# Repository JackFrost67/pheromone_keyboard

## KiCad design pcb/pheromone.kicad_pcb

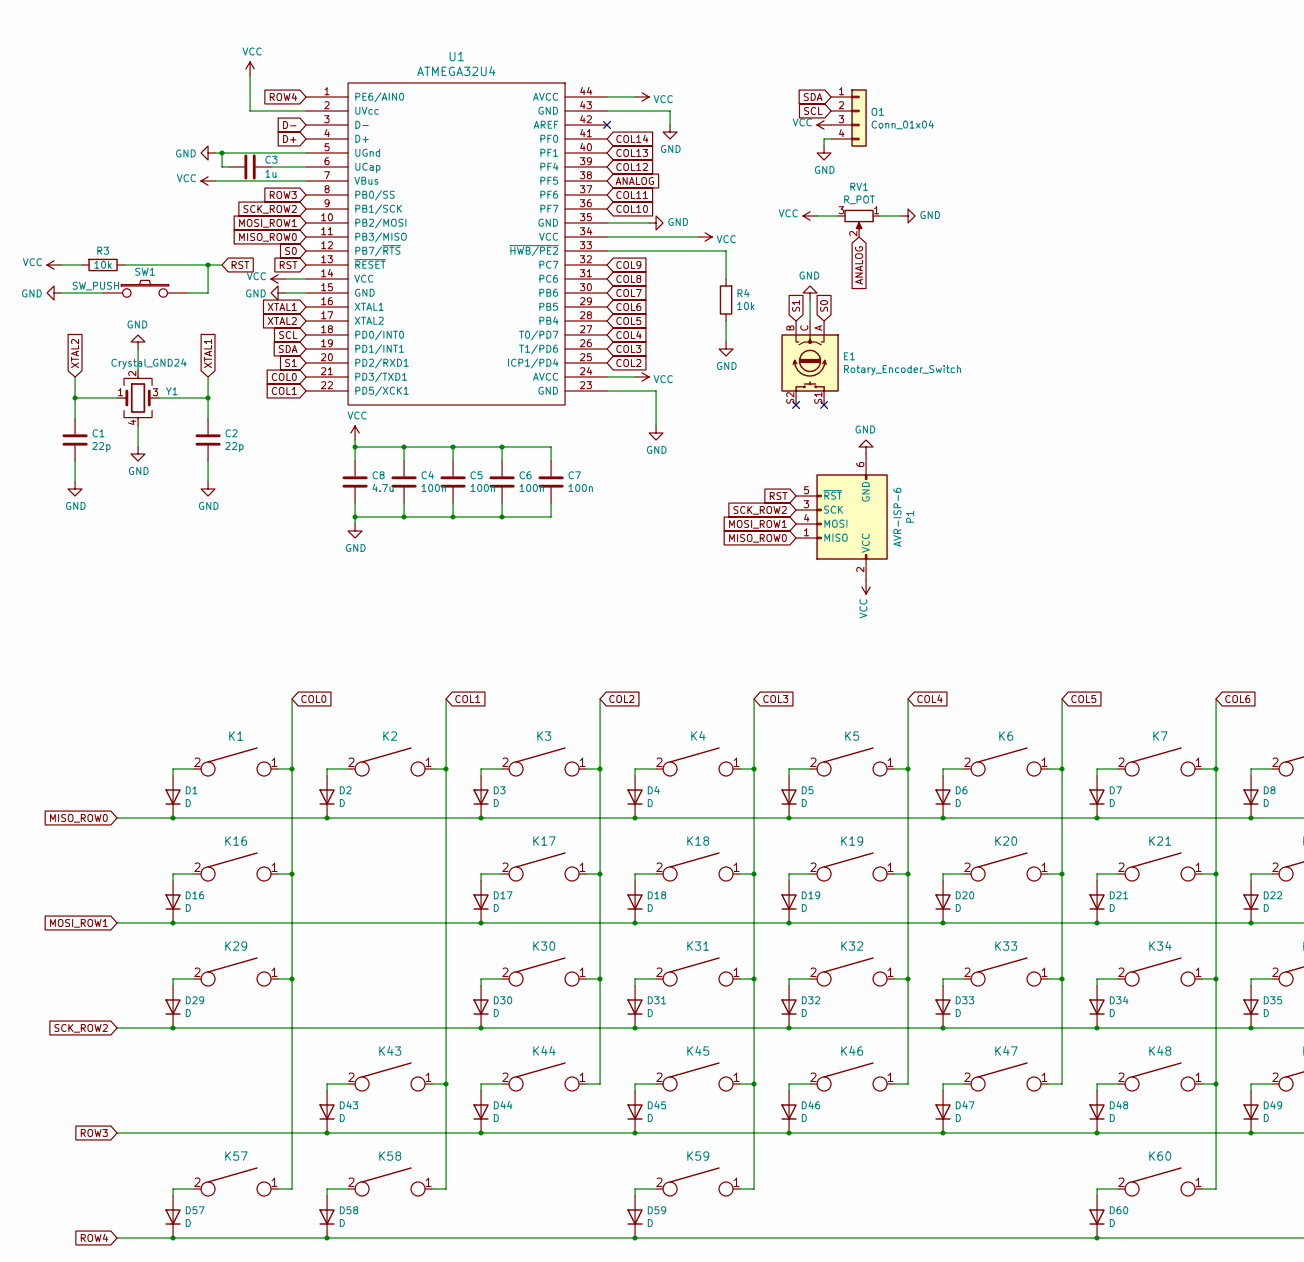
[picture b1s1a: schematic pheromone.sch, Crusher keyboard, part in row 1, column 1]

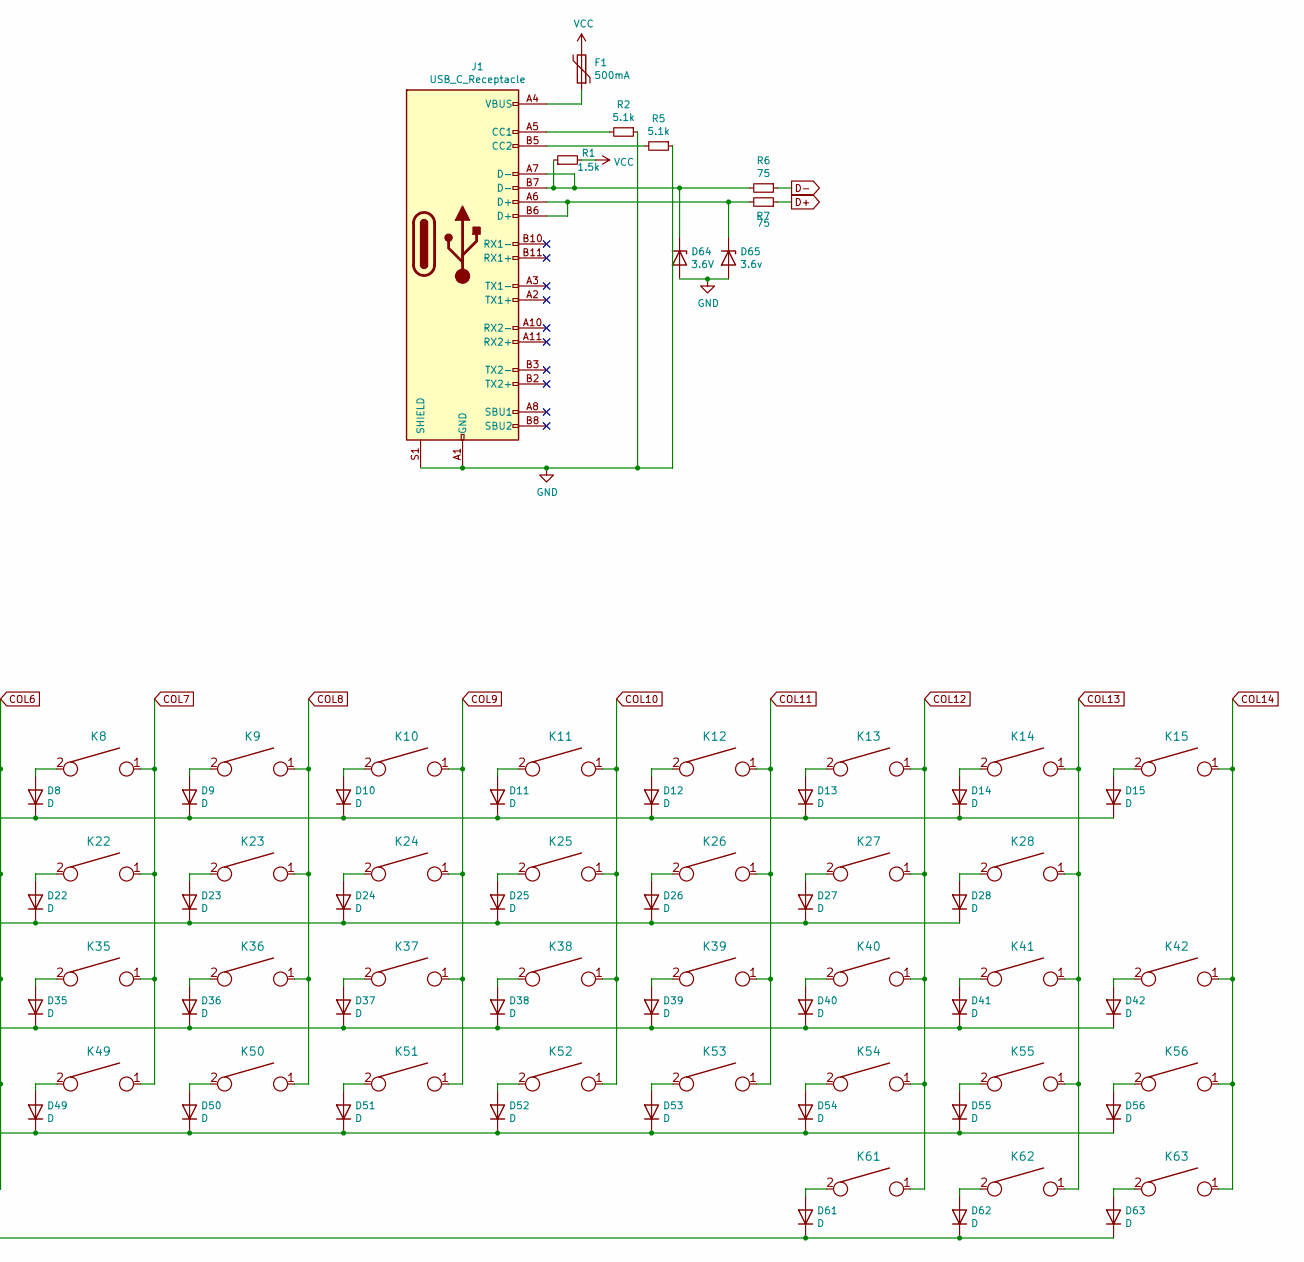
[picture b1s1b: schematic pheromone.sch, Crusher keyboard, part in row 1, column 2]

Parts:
C1, C2: 22p; C_0805_2012Metric
C3: 1u; C_0805_2012Metric
C4, C5, C6, C7: 100n; C_0805_2012Metric
C8: 4.7u; C_0805_2012Metric
D1, D2, D3, D4, D5, D6, D7, D8, D9, D10, D11, D12, D13, D14, D15, D16, D17, D18, D19, D20, D21, D22, D23, D24, D25, D26, D27, D28, D29, D30, D31, D32, D33, D34, D35, D36, D37, D38, D39, D40, D41, D42, D43, D44, D45, D46, D47, D48, D49, D50, D51, D52, D53, D54, D55, D56, D57, D58, D59, D60, D61, D62, D63: D; D_SOD-123
D64: 3.6V; D_SOD-123
D65: 3.6v; D_SOD-123
E1: Rotary_Encoder_Switch; RotaryEncoder_Alps_EC11E-Switch_Vertical_H20mm
F1: 500mA; Fuse_0805_2012Metric
J1: USB_C_Receptacle; USB_C_Receptacle_GCT_USB4085
K1, K2, K3, K4, K5, K6, K7, K8, K9, K10, K11, K12, K13, K14, K15, K17, K18, K19, K20, K21, K22, K23, K24, K25, K26, K27, K28, K30, K31, K32, K33, K34, K35, K36, K37, K38, K39, K40, K41, K44, K45, K46, K47, K48, K49, K50, K51, K52, K53, K54, K55, K56, K61, K62, K63: KEYSW; MXOnly-1U-Hotswap
K16: KEYSW; MXOnly-1.5U-Hotswap
K29: KEYSW; MXOnly-1.75U-Hotswap
K42: KEYSW; MXOnly-ISO-Hotswap
K43: KEYSW; MXOnly-2U-Hotswap-ReversedStabilizers
K57, K58, K59: KEYSW; MXOnly-1.25U-Hotswap
K60: KEYSW; MXOnly-6.25U-Hotswap-ReversedStabilizers
O1: Conn_01x04; 0.91_SSD1306_OLED
P1: AVR-ISP-6; PinHeader_2x03_P2.54mm_Vertical
R1: 1.5k; R_0805_2012Metric
R2, R5: 5.1k; R_0805_2012Metric
R3, R4: 10k; R_0805_2012Metric
R6, R7: 75; R_0805_2012Metric
RV1: R_POT; potentiometer_slider_45mm
SW1: SW_PUSH; SW_DIP_SPSTx01_Slide_6.7x4.1mm_W6.73mm_P2.54mm_LowProfile_J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
U1: ATMEGA32U4; TQFP-44_10x10mm_Pitch0.8mm
Y1: Crystal_GND24; Crystal_SMD_3225-4Pin_3.2x2.5mm

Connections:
ANALOG: RV1.2, U1.38 (PF5)
COL0: K1.1, K16.1, K29.1, K57.1, U1.21 (PD3/TXD1)
COL1: K2.1, K43.1, K58.1, U1.22 (PD5/XCK1)
COL2: K3.1, K17.1, K30.1, K44.1, U1.25 (ICP1/PD4)
COL3: K4.1, K18.1, K31.1, K45.1, K59.1, U1.26 (T1/PD6)
COL4: K5.1, K19.1, K32.1, K46.1, U1.27 (T0/PD7)
COL5: K6.1, K20.1, K33.1, K47.1, U1.28 (PB4)
COL6: K7.1, K21.1, K34.1, K48.1, K60.1, U1.29 (PB5)
COL7: K8.1, K22.1, K35.1, K49.1, U1.30 (PB6)
COL8: K9.1, K23.1, K36.1, K50.1, U1.31 (PC6)
COL9: K10.1, K24.1, K37.1, K51.1, U1.32 (PC7)
COL10: K11.1, K25.1, K38.1, K52.1, U1.36 (PF7)
COL11: K12.1, K26.1, K39.1, K53.1, U1.37 (PF6)
COL12: K13.1, K27.1, K40.1, K54.1, K61.1, U1.39 (PF4)
COL13: K14.1, K28.1, K41.1, K55.1, K62.1, U1.40 (PF1)
COL14: K15.1, K42.1, K56.1, K63.1, U1.41 (PF0)
D+: R7.1, U1.4 (D+)
D-: R6.1, U1.3 (D-)
GND: C1.1, C2.1, C3.1, C4.1, C5.1, C6.1, C7.1, C8.1, D64.2 (A), D65.2 (A), E1.C, J1.A1 (GND), J1.A12 (GND), J1.B1 (GND), J1.B12 (GND), J1.S1 (SHIELD), O1.4, P1.6 (GND), R2.1, R4.1, R5.1, RV1.1, SW1.1, U1.5 (UGnd), U1.15 (GND), U1.23 (GND), U1.35 (GND), U1.43 (GND), Y1.2, Y1.4
MISO_ROW0: D1.1 (K), D2.1 (K), D3.1 (K), D4.1 (K), D5.1 (K), D6.1 (K), D7.1 (K), D8.1 (K), D9.1 (K), D10.1 (K), D11.1 (K), D12.1 (K), D13.1 (K), D14.1 (K), D15.1 (K), P1.1 (MISO), U1.11 (PB3/MISO)
MOSI_ROW1: D16.1 (K), D17.1 (K), D18.1 (K), D19.1 (K), D20.1 (K), D21.1 (K), D22.1 (K), D23.1 (K), D24.1 (K), D25.1 (K), D26.1 (K), D27.1 (K), D28.1 (K), P1.4 (MOSI), U1.10 (PB2/MOSI)
unnamed: C3.2, U1.6 (UCap)
unnamed: D1.2 (A), K1.2
unnamed: D2.2 (A), K2.2
unnamed: D3.2 (A), K3.2
unnamed: D4.2 (A), K4.2
unnamed: D5.2 (A), K5.2
unnamed: D6.2 (A), K6.2
unnamed: D7.2 (A), K7.2
unnamed: D8.2 (A), K8.2
unnamed: D9.2 (A), K9.2
unnamed: D10.2 (A), K10.2
unnamed: D11.2 (A), K11.2
unnamed: D12.2 (A), K12.2
unnamed: D13.2 (A), K13.2
unnamed: D14.2 (A), K14.2
unnamed: D15.2 (A), K15.2
unnamed: D16.2 (A), K16.2
unnamed: D17.2 (A), K17.2
unnamed: D18.2 (A), K18.2
unnamed: D19.2 (A), K19.2
unnamed: D20.2 (A), K20.2
unnamed: D21.2 (A), K21.2
unnamed: D22.2 (A), K22.2
unnamed: D23.2 (A), K23.2
unnamed: D24.2 (A), K24.2
unnamed: D25.2 (A), K25.2
unnamed: D26.2 (A), K26.2
unnamed: D27.2 (A), K27.2
unnamed: D28.2 (A), K28.2
unnamed: D29.2 (A), K29.2
unnamed: D30.2 (A), K30.2
unnamed: D31.2 (A), K31.2
unnamed: D32.2 (A), K32.2
unnamed: D33.2 (A), K33.2
unnamed: D34.2 (A), K34.2
unnamed: D35.2 (A), K35.2
unnamed: D36.2 (A), K36.2
unnamed: D37.2 (A), K37.2
unnamed: D38.2 (A), K38.2
unnamed: D39.2 (A), K39.2
unnamed: D40.2 (A), K40.2
unnamed: D41.2 (A), K41.2
unnamed: D42.2 (A), K42.2
unnamed: D43.2 (A), K43.2
unnamed: D44.2 (A), K44.2
unnamed: D45.2 (A), K45.2
unnamed: D46.2 (A), K46.2
unnamed: D47.2 (A), K47.2
unnamed: D48.2 (A), K48.2
unnamed: D49.2 (A), K49.2
unnamed: D50.2 (A), K50.2
unnamed: D51.2 (A), K51.2
unnamed: D52.2 (A), K52.2
unnamed: D53.2 (A), K53.2
unnamed: D54.2 (A), K54.2
unnamed: D55.2 (A), K55.2
unnamed: D56.2 (A), K56.2
unnamed: D57.2 (A), K57.2
unnamed: D58.2 (A), K58.2
unnamed: D59.2 (A), K59.2
unnamed: D60.2 (A), K60.2
unnamed: D61.2 (A), K61.2
unnamed: D62.2 (A), K62.2
unnamed: D63.2 (A), K63.2
unnamed: D64.1 (K), J1.A7 (D-), J1.B7 (D-), R1.1, R6.2
unnamed: D65.1 (K), J1.A6 (D+), J1.B6 (D+), R7.2
unnamed: F1.1, J1.A4 (VBUS), J1.A9 (VBUS), J1.B4 (VBUS), J1.B9 (VBUS)
unnamed: J1.A5 (CC1), R2.2
unnamed: J1.B5 (CC2), R5.2
unnamed: R4.2, U1.33 (~HWB/PE2)
ROW3: D43.1 (K), D44.1 (K), D45.1 (K), D46.1 (K), D47.1 (K), D48.1 (K), D49.1 (K), D50.1 (K), D51.1 (K), D52.1 (K), D53.1 (K), D54.1 (K), D55.1 (K), D56.1 (K), U1.8 (PB0/SS)
ROW4: D57.1 (K), D58.1 (K), D59.1 (K), D60.1 (K), D61.1 (K), D62.1 (K), D63.1 (K), U1.1 (PE6/AIN0)
RST: P1.5 (~RST), R3.1, SW1.2, U1.13 (~RESET)
S0: E1.A, U1.12 (PB7/~RTS)
S1: E1.B, U1.20 (PD2/RXD1)
SCK_ROW2: D29.1 (K), D30.1 (K), D31.1 (K), D32.1 (K), D33.1 (K), D34.1 (K), D35.1 (K), D36.1 (K), D37.1 (K), D38.1 (K), D39.1 (K), D40.1 (K), D41.1 (K), D42.1 (K), P1.3 (SCK), U1.9 (PB1/SCK)
SCL: O1.2, U1.18 (PD0/INT0)
SDA: O1.1, U1.19 (PD1/INT1)
VCC: C4.2, C5.2, C6.2, C7.2, C8.2, F1.2, O1.3, P1.2 (VCC), R1.2, R3.2, RV1.3, U1.2 (UVcc), U1.7 (VBus), U1.14 (VCC), U1.24 (AVCC), U1.34 (VCC), U1.44 (AVCC)
XTAL1: C2.2, U1.16 (XTAL1), Y1.3
XTAL2: C1.2, U1.17 (XTAL2), Y1.1

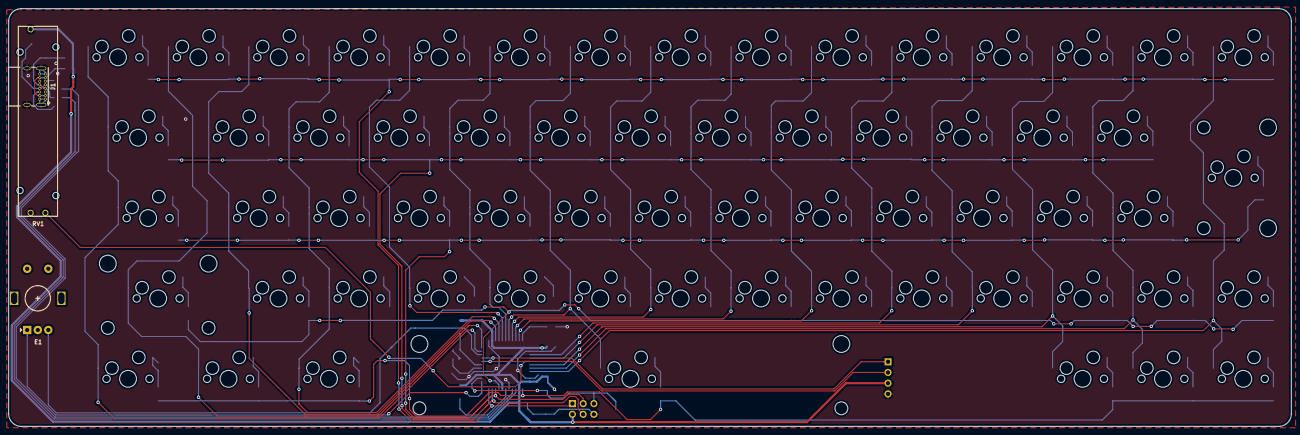
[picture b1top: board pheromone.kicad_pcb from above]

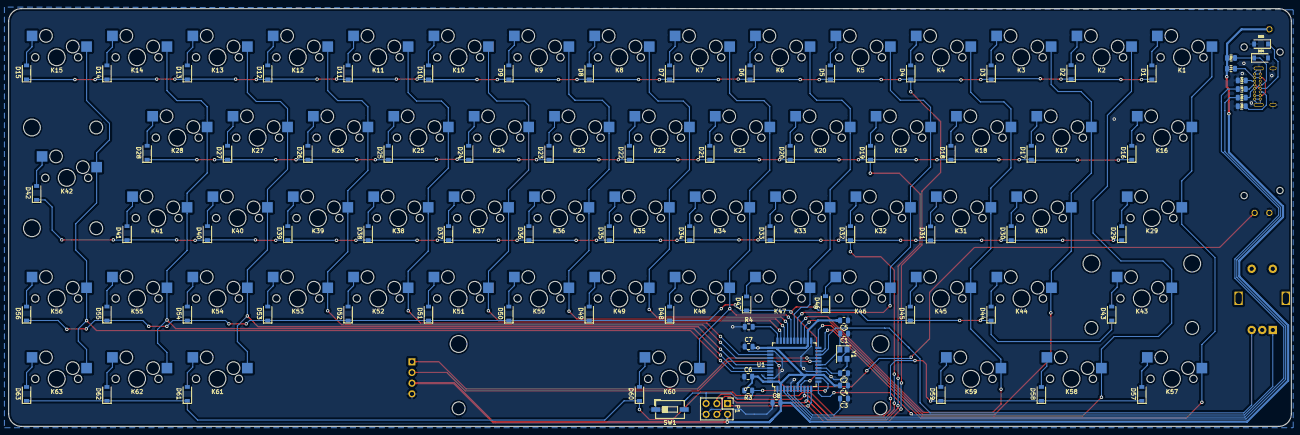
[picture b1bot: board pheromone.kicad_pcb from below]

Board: 2 copper layers, 304.0 x 99.0 mm, 152 parts (85 on the bottom side), 102 nets.

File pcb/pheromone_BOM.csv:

"Id";"Designator";"Package";"Quantity";"Designation";"Supplier and ref";
1;"RV1";"potentiometer_slider_45mm";1;"R_POT";;;
2;"R7,R6";"R_0805_2012Metric";2;"75";;;
3;"R5,R2";"R_0805_2012Metric";2;"5.1k";;;
4;"R1";"R_0805_2012Metric";1;"1.5k";;;
5;"J1";"USB_C_Receptacle_GCT_USB4085";1;"USB_C_Receptacle";;;
6;"F1";"Fuse_0805_2012Metric";1;"500mA";;;
7;"D65";"D_SOD-123";1;"3.6v";;;
8;"D64";"D_SOD-123";1;"3.6V";;;
9;"U1";"TQFP-44_10x10mm_Pitch0.8mm";1;"ATMEGA32U4";;;
10;"R4,R3";"R_0805_2012Metric";2;"10k";;;
11;"C8";"C_0805_2012Metric";1;"4.7u";;;
12;"C7,C6,C5,C4";"C_0805_2012Metric";4;"100n";;;
13;"C3";"C_0805_2012Metric";1;"1u";;;
14;"C2,C1";"C_0805_2012Metric";2;"22p";;;
15;"Y1";"Crystal_SMD_3225-4Pin_3.2x2.5mm";1;"Crystal_GND24";;;
16;"K60";"MXOnly-6.25U-Hotswap-ReversedStabilizers";1;"KEYSW";;;
17;"P1";"PinHeader_2x03_P2.54mm_Vertical";1;"AVR-ISP-6";;;
18;"E1";"RotaryEncoder_Alps_EC11E-Switch_Vertical_H20mm";1;"Rotary_Encoder_Switch";;;
19;"O1";"0.91_SSD1306_OLED";1;"Conn_01x04";;;
20;"K13,K56,K1,K2,K3,K4,K5,K6,K7,K8,K9,K10,K11,K12,K14,K15,K17,K18,K19,K20,K21,K22,K23,K24,K25,K26,K27,K28,K30,K31,K32,K33,K34,K35,K36,K37,K38,K39,K40,K41,K44,K45,K46,K47,K48,K49,K50,K51,K52,K53,K54,K55,K61,K62,K63";"MXOnly-1U-Hotswap";55;"KEYSW";;;
21;"K43";"MXOnly-2U-Hotswap-ReversedStabilizers";1;"KEYSW";;;
22;"K59,K58,K57";"MXOnly-1.25U-Hotswap";3;"KEYSW";;;
23;"D1,D2,D3,D4,D5,D6,D7,D8,D9,D10,D11,D12,D13,D14,D15,D16,D17,D18,D19,D20,D21,D22,D23,D24,D25,D26,D27,D28,D29,D30,D31,D32,D33,D34,D35,D36,D37,D38,D39,D40,D41,D42,D43,D44,D45,D46,D47,D48,D49,D50,D51,D52,D53,D54,D55,D56,D57,D58,D59,D60,D61,D62,D63";"D_SOD-123";63;"D";;;
24;"K16";"MXOnly-1.5U-Hotswap";1;"KEYSW";;;
25;"K29";"MXOnly-1.75U-Hotswap";1;"KEYSW";;;
26;"K42";"MXOnly-ISO-Hotswap";1;"KEYSW";;;
27;"SW1";"SW_DIP_SPSTx01_Slide_6.7x4.1mm_W6.73mm_P2.54mm_LowProfile_JPin";1;"SW_PUSH";;;

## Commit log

2020-08-26 add typec support
2020-08-26 updates pcb
2020-08-28 flip side for typec connector
2020-08-28 update silks and other stuff
